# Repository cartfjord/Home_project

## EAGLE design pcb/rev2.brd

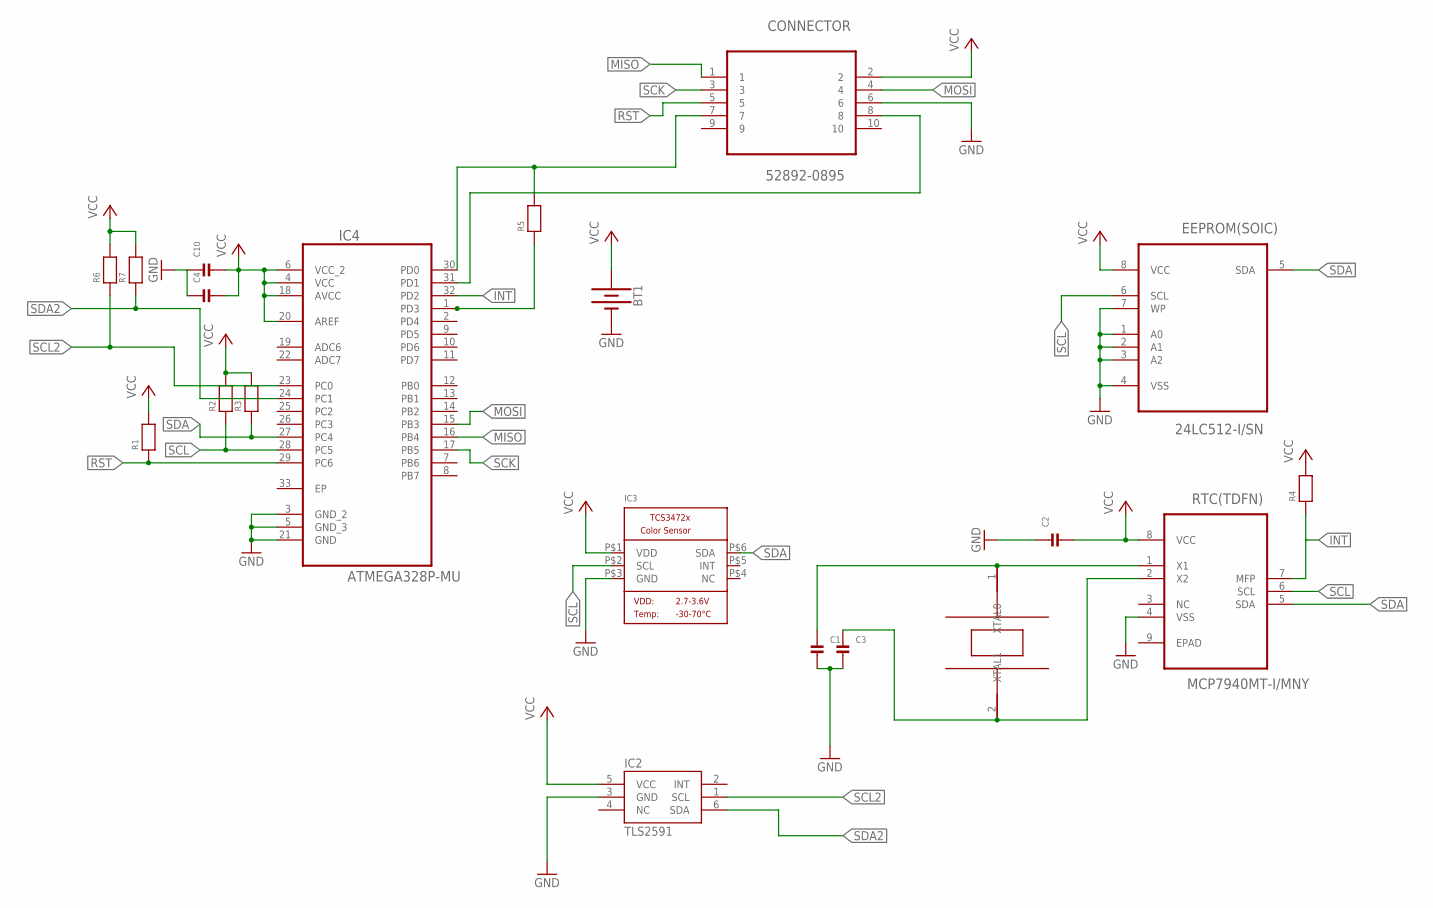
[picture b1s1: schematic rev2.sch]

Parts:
BT1: BATTERY-20MM_SMD_4LEGS; BATTCON_20MM_4LEGS
C1, C2, C3, C4, C10: CAP_CERAMIC0402; 0402
CONNECTOR: 52892-0895; MOLEX_52892-0895
EEPROM(SOIC): 24LC512-I/SN; SOIC127P600X175-8N
IC2: TLS2591; WFDFN6
IC3: LIGHT_TCS3472; TCS3472_FN6
IC4: ATMEGA328P-MU; QFN50P500X500X100-33N
R1, R2, R3, R4, R5, R6, R7: RESISTOR0402; 0402
RTC(TDFN): MCP7940MT-I/MNY; TDFN300X200X80-9N
U$2: FC-135R

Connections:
GND: BT1.NEGATIVE (-), C1.2, C2.1, C3.2, C4.1, C10.1, CONNECTOR.6, EEPROM(SOIC).1 (A0), EEPROM(SOIC).2 (A1), EEPROM(SOIC).3 (A2), EEPROM(SOIC).4 (VSS), EEPROM(SOIC).7 (WP), IC2.3 (GND), IC3.P$3 (GND), IC4.3 (GND_2), IC4.5 (GND_3), IC4.21 (GND), RTC(TDFN).4 (VSS)
INT: IC4.32 (PD2), R4.1, RTC(TDFN).7 (MFP)
MISO: CONNECTOR.1, IC4.16 (PB4)
MOSI: CONNECTOR.4, IC4.15 (PB3)
unnamed: IC4.1 (PD3), R5.1
unnamed: C3.1, RTC(TDFN).2 (X2), U$2.2 (XTAL1)
unnamed: C1.1, RTC(TDFN).1 (X1), U$2.1 (XTAL0)
unnamed: CONNECTOR.7, IC4.30 (PD0), R5.2
unnamed: CONNECTOR.8, IC4.31 (PD1)
RST: CONNECTOR.5, IC4.29 (PC6), R1.1
SCK: CONNECTOR.3, IC4.17 (PB5)
SCL: EEPROM(SOIC).6 (SCL), IC3.P$2 (SCL), IC4.28 (PC5), R2.1
SCL2: IC2.1 (SCL), IC4.23 (PC0), R6.1
SDA: EEPROM(SOIC).5 (SDA), IC3.P$6 (SDA), IC4.27 (PC4), R3.1, RTC(TDFN).5 (SDA)
SDA2: IC2.6 (SDA), IC4.24 (PC1), R7.1
VCC: BT1.POSITIVE@1 (+), BT1.POSITIVE@2 (+), BT1.POSITIVE@3 (+), BT1.POSITIVE@4 (+), C2.2, C4.2, C10.2, CONNECTOR.2, EEPROM(SOIC).8 (VCC), IC2.5 (VCC), IC3.P$1 (VDD), IC4.4 (VCC), IC4.6 (VCC_2), IC4.18 (AVCC), IC4.20 (AREF), R1.2, R2.2, R3.2, R4.2, R6.2, R7.2, RTC(TDFN).8 (VCC)

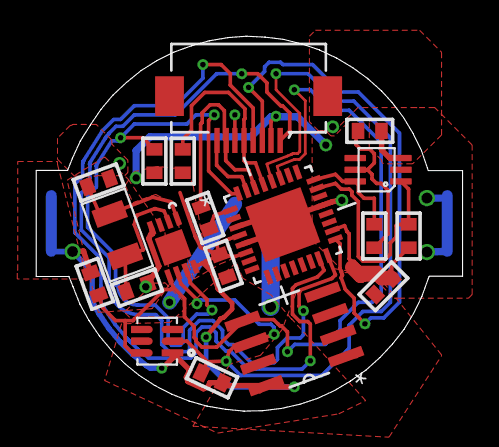
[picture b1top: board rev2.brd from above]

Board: 2 copper layers, 23.7 x 20.8 mm, 20 parts (1 on the bottom side), 16 nets.

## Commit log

2017-08-14 folder structure
2017-08-14 added pcb
2017-08-15 added library for communicating with tsl2591
2017-08-19 started rewriting firmware in pure c
2017-08-22 fixed bug in eeprom
2017-08-22 fixed comment
2017-08-25 added from Oslo

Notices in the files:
parts and their libraries:
SparkFun-Batteries: Licensing: Creative Commons ShareAlike 4.0 International - https://creativecommons.org/licenses/by-sa/4.0
